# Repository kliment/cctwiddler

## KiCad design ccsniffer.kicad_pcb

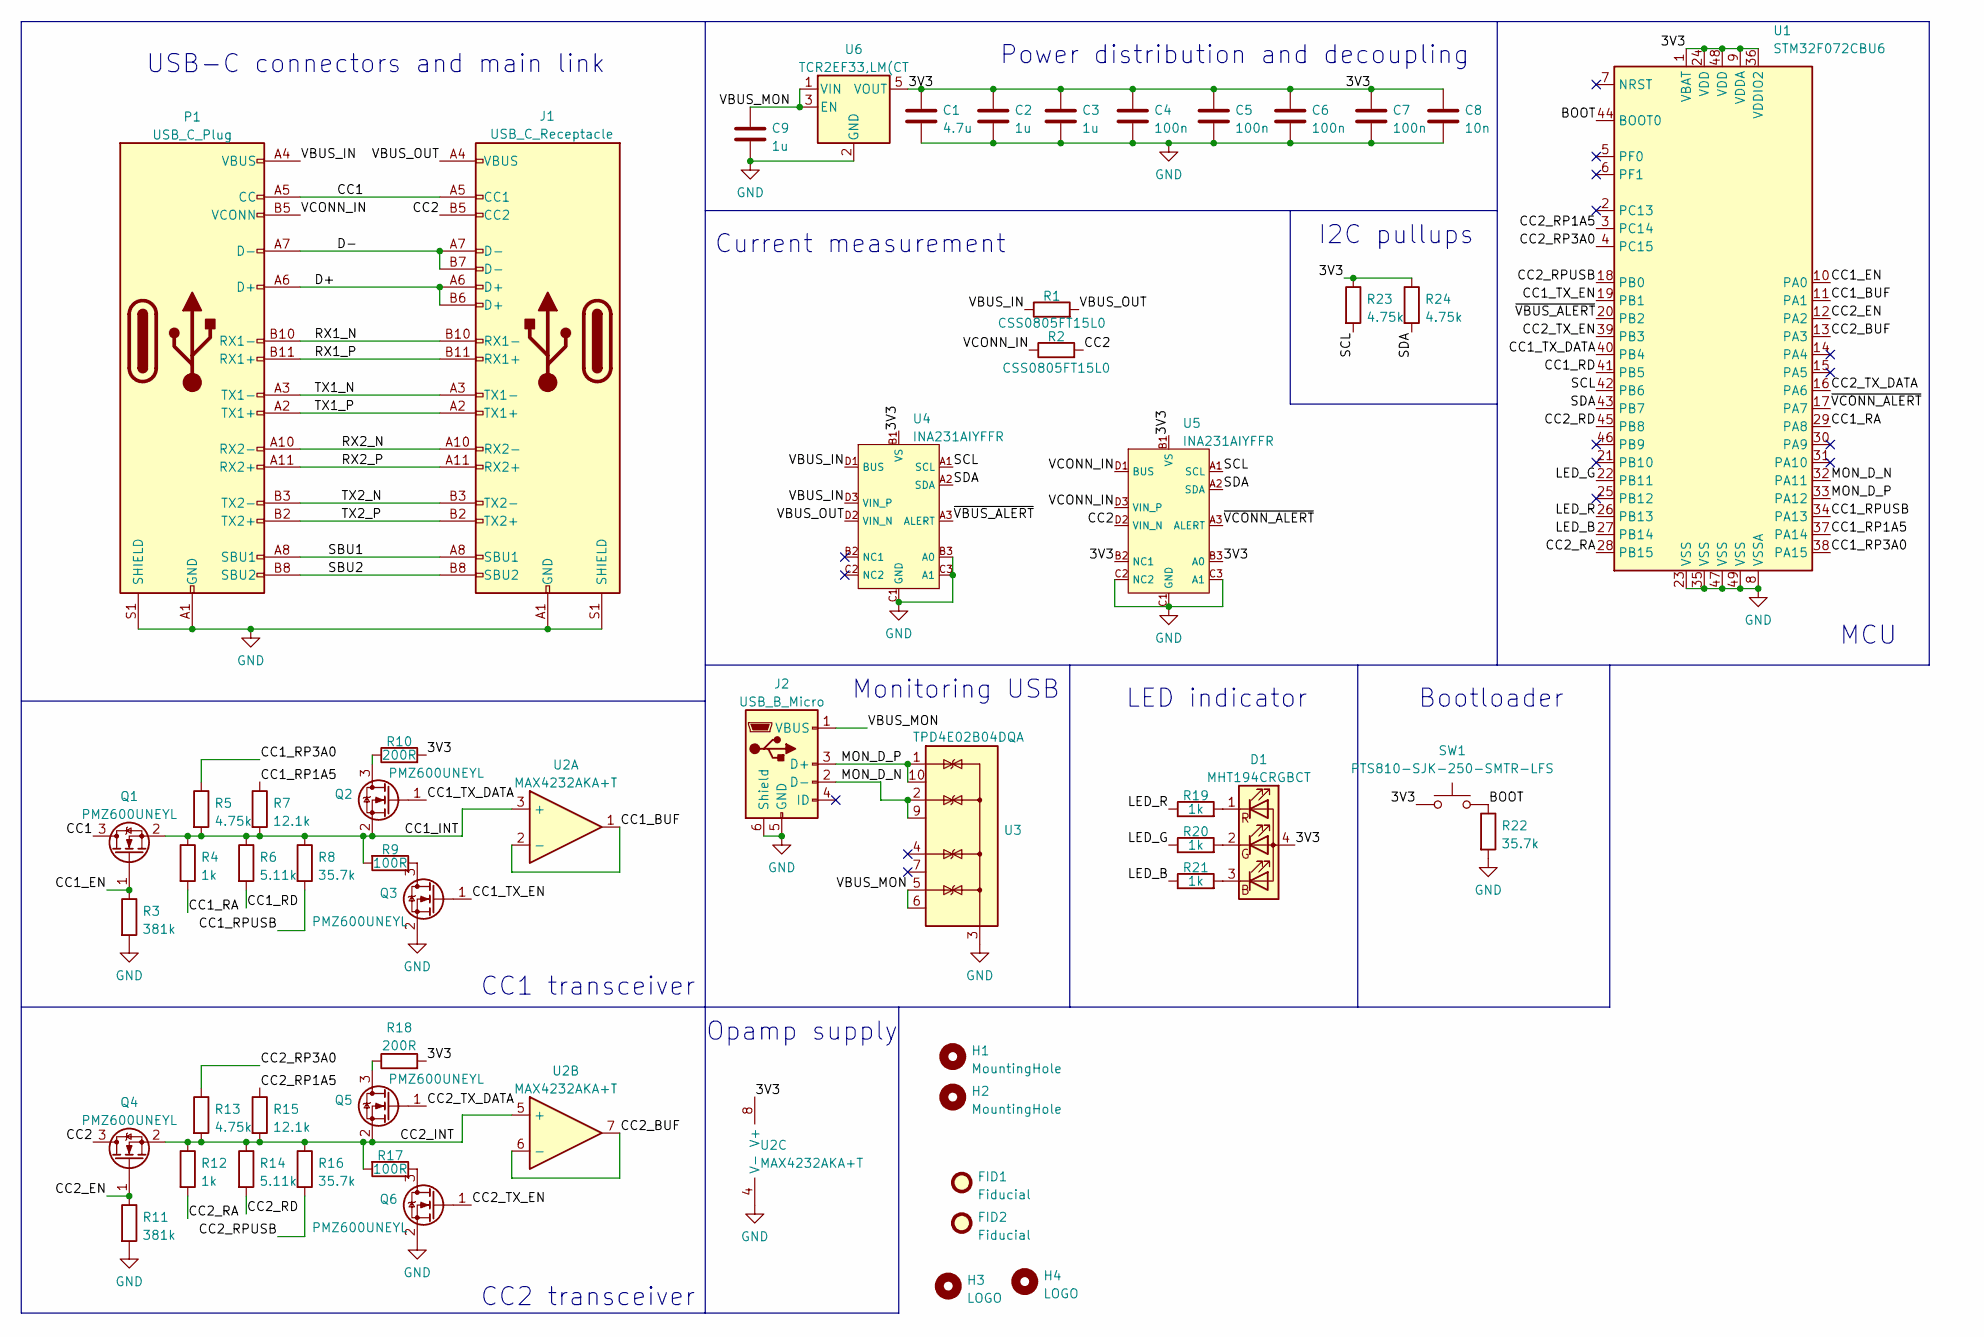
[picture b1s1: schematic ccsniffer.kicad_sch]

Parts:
C1: 4.7u; C_0603_1608Metric
C2, C3, C9: 1u; C_0402_1005Metric
C4, C5, C6, C7: 100n; C_0402_1005Metric
C8: 10n; C_0402_1005Metric
D1: MHT194CRGBCT; LED_LiteOn_LTST-C19HE1WT; LCSC-Partn C404275
FID1, FID2: Fiducial; Fiducial_0.5mm_Mask1mm
H1, H2: MountingHole; MountingHole_2.5mm
H3: LOGO; KiCad-Logo2_5mm_SilkScreen
H4: LOGO; OSHW-Logo_5.7x6mm_SilkScreen
J1: USB_C_Receptacle; USB_C_Receptacle_Amphenol_12401548E4-2A
J2: USB_B_Micro; USB_Micro-B_Amphenol_10118194_Horizontal
P1: USB_C_Plug; USB_C_Plug_JAE_DX07P024AJ1
Q1, Q2, Q3, Q4, Q5, Q6: PMZ600UNEYL; SOT-883
R1, R2: CSS0805FT15L0; R_0805_2012Metric
R3, R11: 381k; R_0402_1005Metric
R4, R12, R19, R20, R21: 1k; R_0402_1005Metric
R5, R13, R23, R24: 4.75k; R_0402_1005Metric
R6, R14: 5.11k; R_0402_1005Metric
R7, R15: 12.1k; R_0402_1005Metric
R8, R16, R22: 35.7k; R_0402_1005Metric
R9, R17: 100R; R_0402_1005Metric
R10, R18: 200R; R_0402_1005Metric
SW1: PTS810-SJK-250-SMTR-LFS; SW_SPST_PTS810
U1: STM32F072CBU6; QFN-48-1EP_7x7mm_P0.5mm_EP5.6x5.6mm
U2: MAX4232AKA+T; SOT-23-8
U3: TPD4E02B04DQA; USON-10_2.5x1.0mm_P0.5mm
U4, U5: INA231AIYFFR; Texas_DSBGA-12_1.65x1.39mm_P0.4mm_YFF0012
U6: TCR2EF33,LM(CT; SC-74A

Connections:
/3V3: C1.1, C2.1, C3.1, C4.1, C5.1, C6.1, C7.1, C8.1, D1.4 (A), R10.2, R18.2, R23.1, R24.1, SW1.1, U1.1 (VBAT), U1.9 (VDDA), U1.24 (VDD), U1.36 (VDDIO2), U1.48 (VDD), U2.8 (V+), U4.B1 (VS), U5.B1 (VS), U5.B2 (NC1), U5.B3 (A0), U6.5 (VOUT)
/BOOT: R22.1, SW1.2, U1.44 (BOOT0)
/CC1: J1.A5 (CC1), P1.A5 (CC), Q1.3 (D)
/CC1_BUF: U1.11 (PA1), U2.1, U2.2 (-)
/CC1_EN: Q1.1 (G), R3.1, U1.10 (PA0)
/CC1_INT: Q1.2 (S), Q2.2 (S), R4.1, R5.2, R6.1, R7.2, R8.1, R9.2, U2.3 (+)
/CC1_RA: R4.2, U1.29 (PA8)
/CC1_RD: R6.2, U1.41 (PB5)
/CC1_RP1A5: R7.1, U1.37 (PA14)
/CC1_RP3A0: R5.1, U1.38 (PA15)
/CC1_RPUSB: R8.2, U1.34 (PA13)
/CC1_TX_DATA: Q2.1 (G), U1.40 (PB4)
/CC1_TX_EN: Q3.1 (G), U1.19 (PB1)
/CC2: J1.B5 (CC2), Q4.3 (D), R2.2, U5.D2 (VIN_N)
/CC2_BUF: U1.13 (PA3), U2.6 (-), U2.7
/CC2_EN: Q4.1 (G), R11.1, U1.12 (PA2)
/CC2_INT: Q4.2 (S), Q5.2 (S), R12.1, R13.2, R14.1, R15.2, R16.1, R17.2, U2.5 (+)
/CC2_RA: R12.2, U1.28 (PB15)
/CC2_RD: R14.2, U1.45 (PB8)
/CC2_RP1A5: R15.1, U1.3 (PC14)
/CC2_RP3A0: R13.1, U1.4 (PC15)
/CC2_RPUSB: R16.2, U1.18 (PB0)
/CC2_TX_DATA: Q5.1 (G), U1.16 (PA6)
/CC2_TX_EN: Q6.1 (G), U1.39 (PB3)
/D+: J1.A6 (D+), J1.B6 (D+), P1.A6 (D+)
/D-: J1.A7 (D-), J1.B7 (D-), P1.A7 (D-)
/LED_B: R21.1, U1.27 (PB14)
/LED_G: R20.1, U1.22 (PB11)
/LED_R: R19.1, U1.26 (PB13)
/MON_D_N: J2.2 (D-), U1.32 (PA11), U3.2 (IO2), U3.9 (NC)
/MON_D_P: J2.3 (D+), U1.33 (PA12), U3.1 (IO1), U3.10 (NC)
/RX1_N: J1.B10 (RX1-), P1.B10 (RX1-)
/RX1_P: J1.B11 (RX1+), P1.B11 (RX1+)
/RX2_N: J1.A10 (RX2-), P1.A10 (RX2-)
/RX2_P: J1.A11 (RX2+), P1.A11 (RX2+)
/SBU1: J1.A8 (SBU1), P1.A8 (SBU1)
/SBU2: J1.B8 (SBU2), P1.B8 (SBU2)
/SCL: R23.2, U1.42 (PB6), U4.A1 (SCL), U5.A1 (SCL)
/SDA: R24.2, U1.43 (PB7), U4.A2 (SDA), U5.A2 (SDA)
/TX1_N: J1.A3 (TX1-), P1.A3 (TX1-)
/TX1_P: J1.A2 (TX1+), P1.A2 (TX1+)
/TX2_N: J1.B3 (TX2-), P1.B3 (TX2-)
/TX2_P: J1.B2 (TX2+), P1.B2 (TX2+)
/VBUS_IN: P1.A4 (VBUS), P1.A9 (VBUS), P1.B4 (VBUS), P1.B9 (VBUS), R1.1, U4.D1 (BUS), U4.D3 (VIN_P)
/VBUS_MON: C9.1, J2.1 (VBUS), U3.5 (IO4), U3.6 (NC), U6.1 (VIN), U6.3 (EN)
/VBUS_OUT: J1.A4 (VBUS), J1.A9 (VBUS), J1.B4 (VBUS), J1.B9 (VBUS), R1.2, U4.D2 (VIN_N)
/VCONN_IN: P1.B5 (VCONN), R2.1, U5.D1 (BUS), U5.D3 (VIN_P)
/~VBUS_ALERT: U1.20 (PB2), U4.A3 (ALERT)
/~VCONN_ALERT: U1.17 (PA7), U5.A3 (ALERT)
GND: C1.2, C2.2, C3.2, C4.2, C5.2, C6.2, C7.2, C8.2, C9.2, J1.A1 (GND), J1.A12 (GND), J1.B1 (GND), J1.B12 (GND), J1.S1 (SHIELD), J2.5 (GND), J2.6 (Shield), P1.A1 (GND), P1.A12 (GND), P1.B1 (GND), P1.B12 (GND), P1.S1 (SHIELD), Q3.2 (S), Q6.2 (S), R3.2, R11.2, R22.2, U1.8 (VSSA), U1.23 (VSS), U1.35 (VSS), U1.47 (VSS), U1.49 (VSS), U2.4 (V-), U3.3 (G), U3.8 (G), U4.B3 (A0), U4.C1 (GND), U4.C3 (A1), U5.C1 (GND), U5.C2 (NC2), U5.C3 (A1), U6.2 (GND)
unnamed: D1.1 (RK), R19.2
unnamed: D1.2 (GK), R20.2
unnamed: D1.3 (BK), R21.2
unnamed: Q2.3 (D), R10.1
unnamed: Q3.3 (D), R9.1
unnamed: Q5.3 (D), R18.1
unnamed: Q6.3 (D), R17.1

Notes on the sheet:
LED indicator
I2C pullups
Monitoring USB
Opamp supply
CC1 transceiver
Bootloader
MCU
Current measurement
USB-C connectors and main link
CC2 transceiver
Power distribution and decoupling

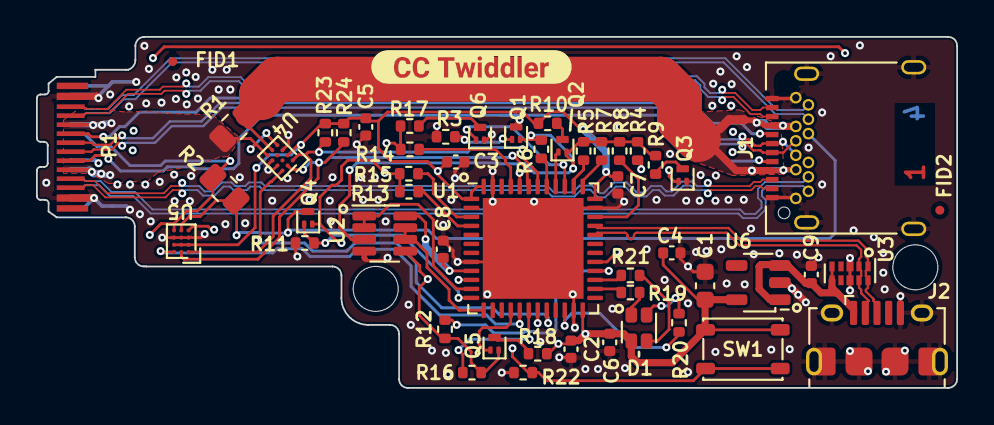
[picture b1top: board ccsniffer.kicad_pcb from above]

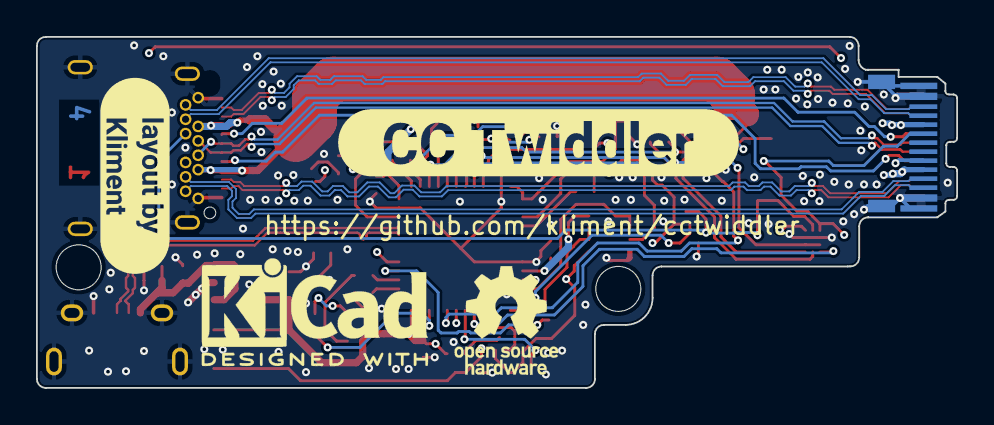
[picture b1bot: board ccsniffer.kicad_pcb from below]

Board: 4 copper layers, 51.1 x 19.5 mm, 59 parts (4 on the bottom side), 57 nets.

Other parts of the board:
kibuzzard-63CB0A6D: G***; kibuzzard-63CB0A6D
kibuzzard-63CB0ABC: G***; kibuzzard-63CB0ABC
kibuzzard-63CB09FB: G***; kibuzzard-63CB09FB

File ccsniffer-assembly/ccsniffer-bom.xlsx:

LIN | RD | Value | Footprint | Quantity | Description | Note | Manufacturer | MPN | Distributor | DPN | URL
1 | C1 | 4.7u | Capacitor_SMD:C_0603_1608Metric | 1 | Capacitor 4.7uF 16V X7R 0603
2 | C2, C3, C9 | 1u | Capacitor_SMD:C_0402_1005Metric | 3 | Capacitor 1uF 10V X7R 0402
3 | C4-C7 | 100n | Capacitor_SMD:C_0402_1005Metric | 4 | Capacitor 100nF 25V X7R 0402
4 | C8 | 10n | Capacitor_SMD:C_0402_1005Metric | 1 | Capacitor 10nF 25V X7R 0402
5 | D1 | MHT194CRGBCT | LED_SMD:LED_LiteOn_LTST-C19HE1WT | 1 | RGB LED |  | Meihua | MHT194CRGBCT | LCSC | C404275 | https://www.lcsc.com/product-detail/Light-Emitting-Diodes-LE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
6 | J1 | USB_C_Receptacle | Connector_USB:USB_C_Receptacle_Amphenol_12401548E4-2A | 1 | USB-C 3.1 receptacle hybrid | This part is difficult to source | Amphenol | 12401548E4#2A
7 | J2 | USB_B_Micro | Connector_USB:USB_Micro-B_Amphenol_10118194_Horizontal | 1 | Micro-USB connector |  | Amphenol | 10118194-0001LF
8 | P1 | USB_C_Plug | Connector_USB:USB_C_Plug_JAE_DX07P024AJ1 | 1 | USB-C connector side mount |  | JAE Electronics | DX07P024AJ1R1500 | LCSC | C5352764 | https://www.lcsc.com/product-detail/USB-Connectors_JAE-Elect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
9 | Q1-Q6 | PMZ600UNEYL | Package_TO_SOT_SMD:SOT-883 | 6 | N-channel MOSFET |  | Nexperia | PMZ600UNEYL | LCSC | C547286 | https://www.lcsc.com/product-detail/MOSFETs_Nexperia-PMZ600U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
10 | R1, R2 | CSS0805FT15L0 | Resistor_SMD:R_0805_2012Metric | 2 | Current sense R 15mOhm 0.5W 1% 0805 |  | Stackpole Electronics | CSS0805FT15L0 | Digikey |  | https://www.digikey.de/de/products/detail/stackpole-electron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
11 | R3, R11 | 381k | Resistor_SMD:R_0402_1005Metric | 2 | Resistor 381k 1% 0402
12 | R6, R14 | 5.1k | Resistor_SMD:R_0402_1005Metric | 2 | Resistor 5.1k 1% 0402
13 | R7, R15 | 12.1k | Resistor_SMD:R_0402_1005Metric | 2 | Resistor 12.1k 1% 0402
14 | R9, R17 | 100R | Resistor_SMD:R_0402_1005Metric | 2 | Resistor 100R 1% 0402
15 | R10, R18 | 200R | Resistor_SMD:R_0402_1005Metric | 2 | Resistor 200R 1% 0402
16 | R4, R12, R19-R21 | 1k | Resistor_SMD:R_0402_1005Metric | 5 | Resistor 1k 1% 0402
17 | R8, R16, R22 | 35.7k | Resistor_SMD:R_0402_1005Metric | 3 | Resistor 35.7k 1% 0402
18 | R5, R13, R23, R24 | 4.75k | Resistor_SMD:R_0402_1005Metric | 4 | Resistor 4.75k 1% 0402
19 | SW1 | PTS810-SJK-250-SMTR-LFS | Button_Switch_SMD:SW_SPST_PTS810 | 1 | Push button |  | C&K | PTS810-SJK-250-SMTR-LFS | LCSC | C221896 | https://www.lcsc.com/product-detail/Tactile-Switches_C-K-PTS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
20 | U1 | STM32F072CBU6 | Package_DFN_QFN:QFN-48-1EP_7x7mm_P0.5mm_EP5.6x5.6mm | 1 | Microcontroller Cortex-M0 |  | STMicroelectronics | STM32F072CBU6 | LCSC | C92504 | https://www.lcsc.com/product-detail/Microcontroller-Units-MC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
21 | U2 | MAX4232AKA+T | Package_TO_SOT_SMD:SOT-23-8 | 1 | Dual opamp SOT-23-8 |  | Analog Devices | MAX4232AKA+T | LCSC | C87614 | https://www.lcsc.com/product-detail/Operational-Amplifier_An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
22 | U3 | TPD4E02B04DQA | Package_SON:USON-10_2.5x1.0mm_P0.5mm | 1 | ESD protection array |  | TI | TPD4E02B04DQA | LCSC | C106794 | https://www.lcsc.com/product-detail/ESD-Protection-Devices_T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
23 | U4, U5 | INA231AIYFFR | ccsnifferparts:Texas_DSBGA-12_1.65x1.39mm_P0.4mm_YFF0012 | 2 | Current sensor IC |  | TI | INA231AIYFFR | Digikey |  | https://www.digikey.de/en/products/detail/INA231AIYFFR/296-4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
24 | U6 | TCR2EF33,LM(CT | ccsnifferparts:SC-74A | 1 | Voltage regulator 3.3V SC-74A |  | Toshiba | TCR2EF33,LM(CT | LCSC | C843273 | https://www.lcsc.com/product-detail/Linear-Voltage-Regulator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
